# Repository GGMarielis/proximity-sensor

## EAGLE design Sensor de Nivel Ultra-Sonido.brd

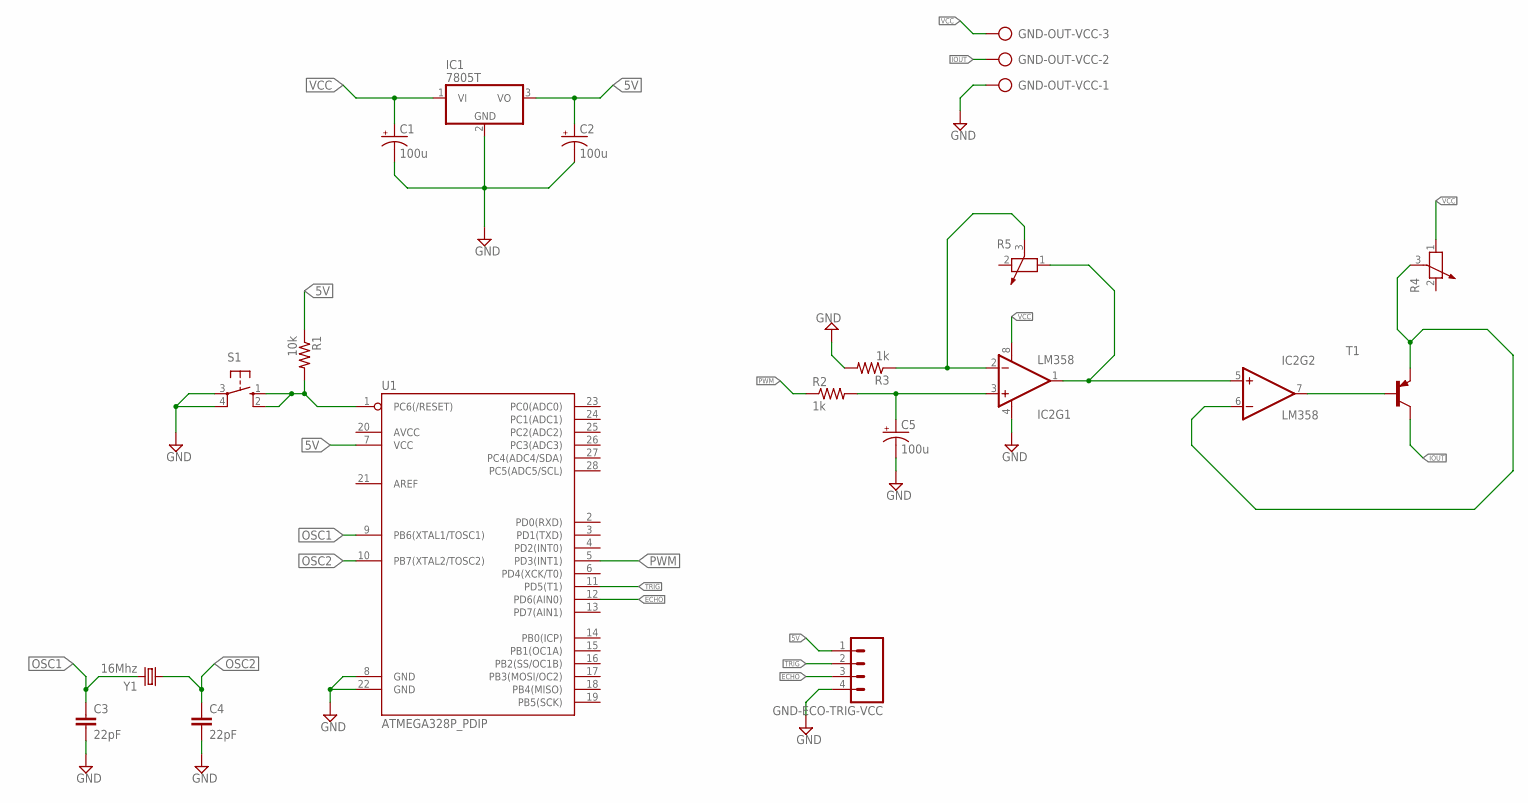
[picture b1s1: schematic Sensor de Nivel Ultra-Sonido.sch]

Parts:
C1, C2, C5: 100u; CPOL-RADIAL-10UF-25V-KIT
C3, C4: 22pF; CAP-PTH-SMALL-KIT
GND-ECO-TRIG-VCC: M04LONGPADS; 1X04_LONGPADS
GND-OUT-VCC: AK500/3
IC1: 7805T; TO220H
IC2: LM358; DIP08
R1: 10k; AXIAL-0.3-KIT
R2, R3: 1k; AXIAL-0.3-KIT
R4, R5: POTENTIOMETER_PT_SPIN; PT-SPIN
S1: 10-XX; B3F-10XX
T1: BC558A-PNP-TO92-EBC; TO92-EBC
U1: ATMEGA328P_PDIP; DIL28-3
Y1: 16Mhz; HC49US

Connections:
5V: C2.1 (+), GND-ECO-TRIG-VCC.1, IC1.3 (VO), R1.P$1 (1), U1.7 (VCC)
ECHO: GND-ECO-TRIG-VCC.3, U1.12 (PD6(AIN0))
GND: C1.2 (-), C2.2 (-), C3.2, C4.2, C5.2 (-), GND-ECO-TRIG-VCC.4, GND-OUT-VCC.1, IC1.2 (GND), IC2.4 (V-), R3.P$2 (2), S1.3, S1.4 (P1), U1.8 (GND), U1.22 (GND)
IOUT: GND-OUT-VCC.2, T1.C
unnamed: R1.P$2 (2), S1.1 (S), S1.2 (S1), U1.1 (PC6(/RESET))
unnamed: C5.1 (+), IC2.3 (+IN), R2.P$2 (2)
unnamed: IC2.2 (-IN), R3.P$1 (1), R5.3
unnamed: IC2.7 (OUT), T1.B
unnamed: IC2.1 (OUT), IC2.5 (+IN), R5.1
unnamed: IC2.6 (-IN), R4.3, T1.E
OSC1: C3.1, U1.9 (PB6(XTAL1/TOSC1)), Y1.2
OSC2: C4.1, U1.10 (PB7(XTAL2/TOSC2)), Y1.1
PWM: R2.P$1 (1), U1.5 (PD3(INT1))
TRIG: GND-ECO-TRIG-VCC.2, U1.11 (PD5(T1))
VCC: C1.1 (+), GND-OUT-VCC.3, IC1.1 (VI), IC2.8 (V+), R4.1

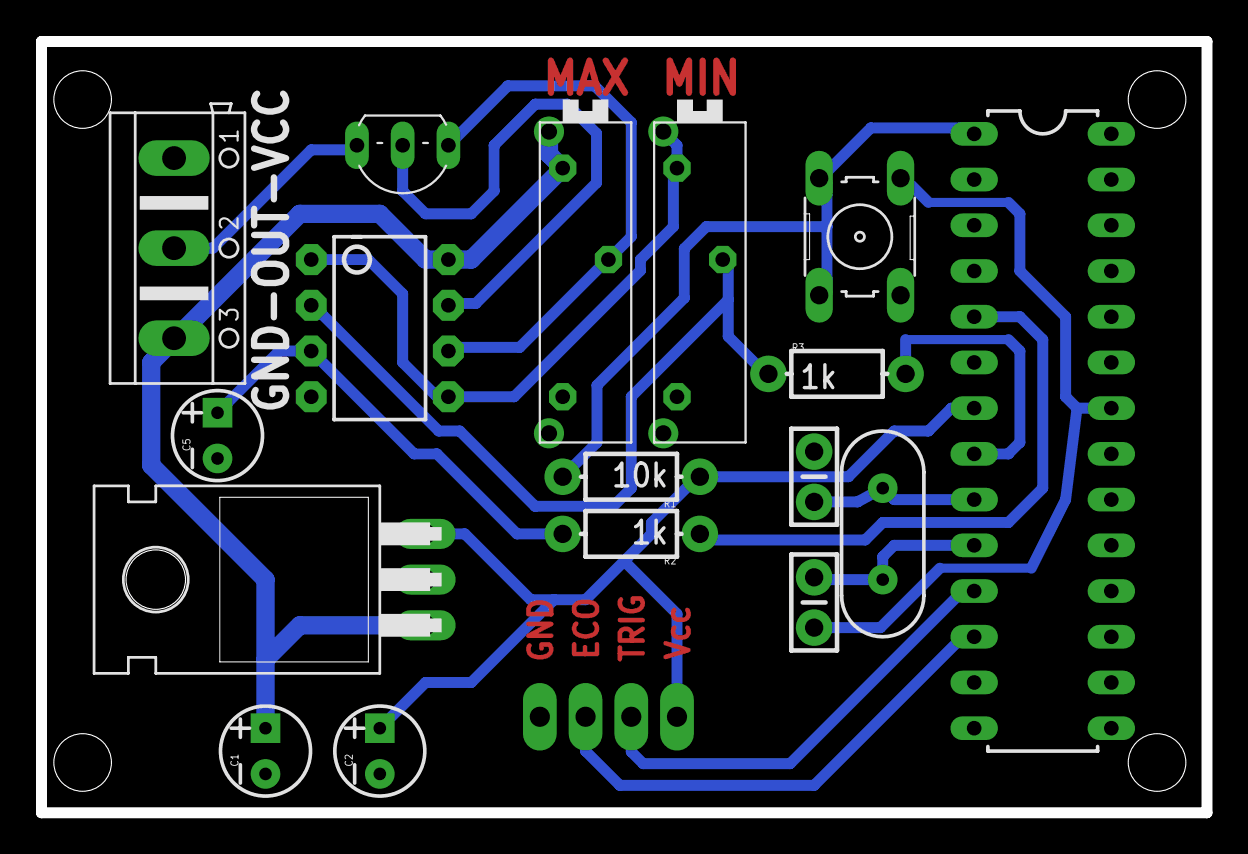
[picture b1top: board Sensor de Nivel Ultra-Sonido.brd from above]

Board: 2 copper layers, 64.8 x 42.9 mm, 18 parts (1 on the bottom side), 15 nets.

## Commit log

2019-07-07 Organize PCB layout files
2019-07-07 Add ccs test to LCD 128x64

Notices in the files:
parts and their libraries:
SparkFun-Capacitors: Licensing: Creative Commons ShareAlike 4.0 International - https://creativecommons.org/licenses/by-sa/4.0
